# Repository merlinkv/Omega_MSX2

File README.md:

# Omega_MSX2
Update of the Omega Home Computer Project

# Original description

This project is an open source implementation of an MSX2 compatible computer. The project is built using a combination of 1980's era components - Z80 CPU, V9958 VDP, AY-3-8910/YM2149F PSG, 8255 PPI, 7400-series logic, and some newer components, such as 512 KiB SRAM and 512 KiB Flash ROM and a few simple programmable logic devices (ATF16V8B SPLDs).

# Keyboard PCB

* 14-04-2024
   - Version updated to 1.2 MKV
   - Schematics, PCB and Gerbers successfully ported to KiCad 8.0.1
   - The board has been rerouted.
   - Some components are now SMD
   - [Interactive BOM](https://htmlpreview.github.io/?https://github.com/merlinkv/Omega_MSX2/blob/main/Omega%20MSX%20Keyboard%201.2%20MKV.html)

# Mainboard PCB

* 10-05-2024
   - Added positility to select the connection type of Slots pin 44 (by SPDT switch SW3). They can be connected to GND (normal) or to NMI.
   - [Interactive BOM](https://htmlpreview.github.io/?https://github.com/merlinkv/Omega_MSX2/blob/main/Omega%20MSX%20Mainboard%201.2.7%20MKV.html)
* 20-04-2024
   - Version updated to 1.2.7 MKV
   - Power lines design has been changed.
   - Board has been re-routed.
* 14-04-2024
   - Version updated to 1.2.6 MKV
   - Schematics, PCB and Gerbers successfully ported to KiCad 8.0.1
   - The board has been re-routed.

# July 18, 2023

Added new ROMs.

# Mainboard PCB 1.2.5 MKV

* Improved routing parameters resulting on a bit more clear video & audio. In my opinion, before the RGB image was very good, now is really great.
* Power Switch footprint modified to, if desired, allow solder big section wires.
* Added another +5v Extra Power connector. The idea is to use it with horizontal pins and connect one small 4x4cm fan on top of the V9958.
* Board is tested working 100% with F4-FMPAC & o4Mega (4MB RAM) modules, internal Gotek with LCD 16x2 screen, cartridges Carnivore 2 & TDC-600 (floppy controller) at the same time with one **5.2v/3A** PSU

# Mainboard PCB 1.2 MKV

* Added possibility to use up to four different ROMs (two PLCC32 IC's).
* Added extra footprints for ROM selection switches.
* Changed internal FDD power connector to a better position.
* Changed all routing parameters and a couple of silk errors corrected.

# Mainboard PCB 1.1 MKV

Omega Mainboard PCB 1.1 MKV is a variant of the Mainboards 1.4US & 1.4EU by Sergey Kiselev & Jordi Solis

All "standard" capacitors, resistors & inductors are now in SMD 1206 format and placed at the bottom of the PCB.

New footprints for internal/external connections:

* 5-pins connector for DC-DC converter (+5v IN - +12v/-12v OUT)
* 2-pins connector for Power ON-OFF switch
* Two Extra Power connectors +5v (2-pins)
* One Extra Power connector +12v/-12v (3-pins)
* Connector for FM-PAC Module (AMP-GND, 2-pins)
* Connector for FM-PAC Power (+12v/-12v, 3-pins)
* Connector for RGB & Composite video (5-pins)
* Connector for S-Video (3-pins)
* Connector for Audio (Mono, 2-pins)
* Separate connectors for NMI & RESET (2-pins each)
* NMI signal connected to pin 44 of each slots (MSX3 Update?)
* FDD Power Connector (+5v/+12v, 4-pins)

# Notes

* Electrolytic capacitors: I recommend to use High Frequency and Low ESR ones.
* SMD resistors: Best is to use ones with 1% tolerance. All must be 1/4w.
* SMD capacitors: I recommend to use X7R type (10%) or less tolerance.
* ROM: AM29F040, SST39SF040 or compatible IC's can be used.
* SPLD's: ATF16V8B or GAL16V8B can be used without needed to use new jed's.
* For power cable and power switch best is to use wires with big section.
* At the moment I recommend to use one **5.2v/3A PSU**.
* It's possible to use one **5.5v/3A** PSU (near the limits but it's inside the power range).

# Links

* https://www.winuaespanol.com/phpbb3/viewtopic.php?p=13291#p13291
* https://github.com/skiselev/omega
* https://www.va-de-retro.com/foros/viewtopic.php?f=17&t=9304&start=40#p168183
* http://retrowiki.es/viewtopic.php?f=49&t=200037057&start=32#p200145495

# Images

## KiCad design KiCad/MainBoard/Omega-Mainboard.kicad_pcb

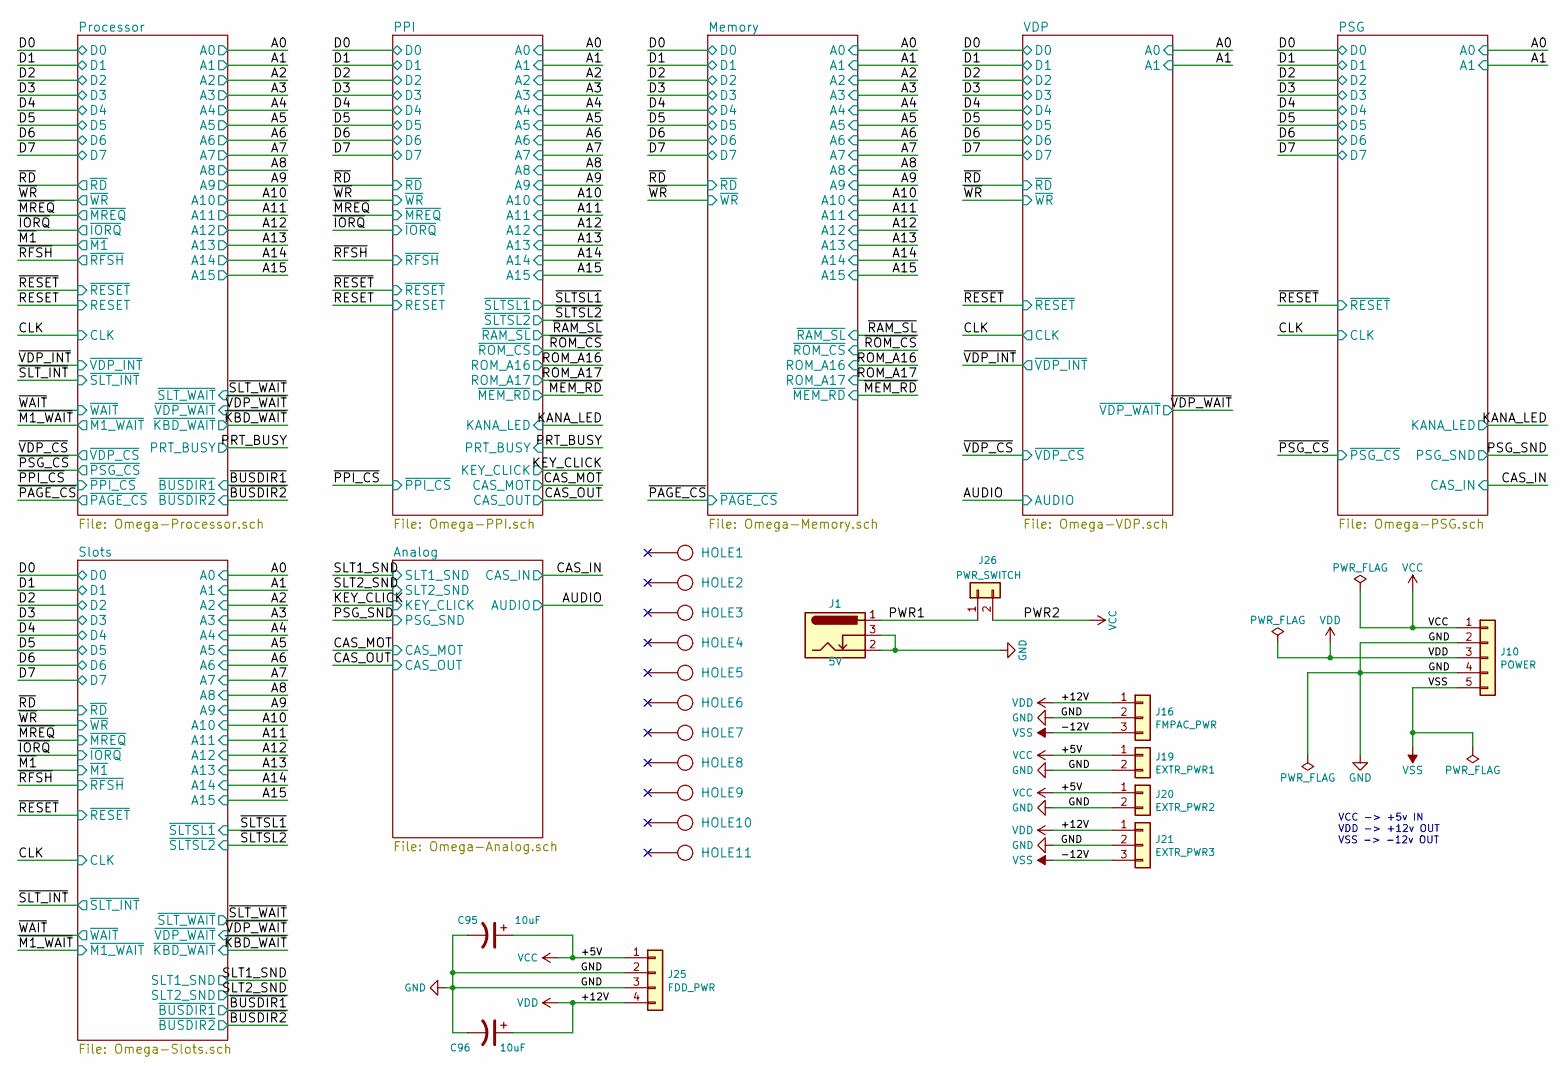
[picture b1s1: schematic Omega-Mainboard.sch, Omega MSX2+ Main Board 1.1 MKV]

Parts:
C95, C96: 10uF; CP_Radial_D5.0mm_P2.50mm
HOLE1, HOLE2, HOLE3, HOLE4, HOLE5, HOLE6, HOLE7, HOLE8, HOLE9, HOLE10, HOLE11: HOLE; MountingHole_3mm_Pad
J1: 5V; BarrelJack_Horizontal
J10: POWER; Molex_KK-254_AE-6410-05A_1x05_P2.54mm_Vertical
J16: FMPAC_PWR; Molex_KK-254_AE-6410-03A_1x03_P2.54mm_Vertical
J19: EXTR_PWR1; Molex_KK-254_AE-6410-02A_1x02_P2.54mm_Vertical
J20: EXTR_PWR2; Molex_KK-254_AE-6410-02A_1x02_P2.54mm_Vertical
J21: EXTR_PWR3; Molex_KK-254_AE-6410-03A_1x03_P2.54mm_Vertical
J25: FDD_PWR; PinHeader_1x04_P2.54mm_Horizontal
J26: PWR_SWITCH; Molex_KK-254_AE-6410-02A_1x02_P2.54mm_Vertical

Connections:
/PWR1: J1.1, J26.1
GND: C95.2, C96.2, J1.2, J1.3, J10.2, J10.4, J16.2, J19.2, J20.2, J21.2, J25.2, J25.3; also elsewhere on the board
VCC: C95.1, J10.1, J19.1, J20.1, J25.1, J26.2; also elsewhere on the board
VDD: C96.1, J10.3, J16.1, J21.1, J25.4; also elsewhere on the board
VSS: J10.5, J16.3, J21.3; also elsewhere on the board

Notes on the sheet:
VCC -> +5v IN VDD -> +12v OUT VSS -> -12v OUT

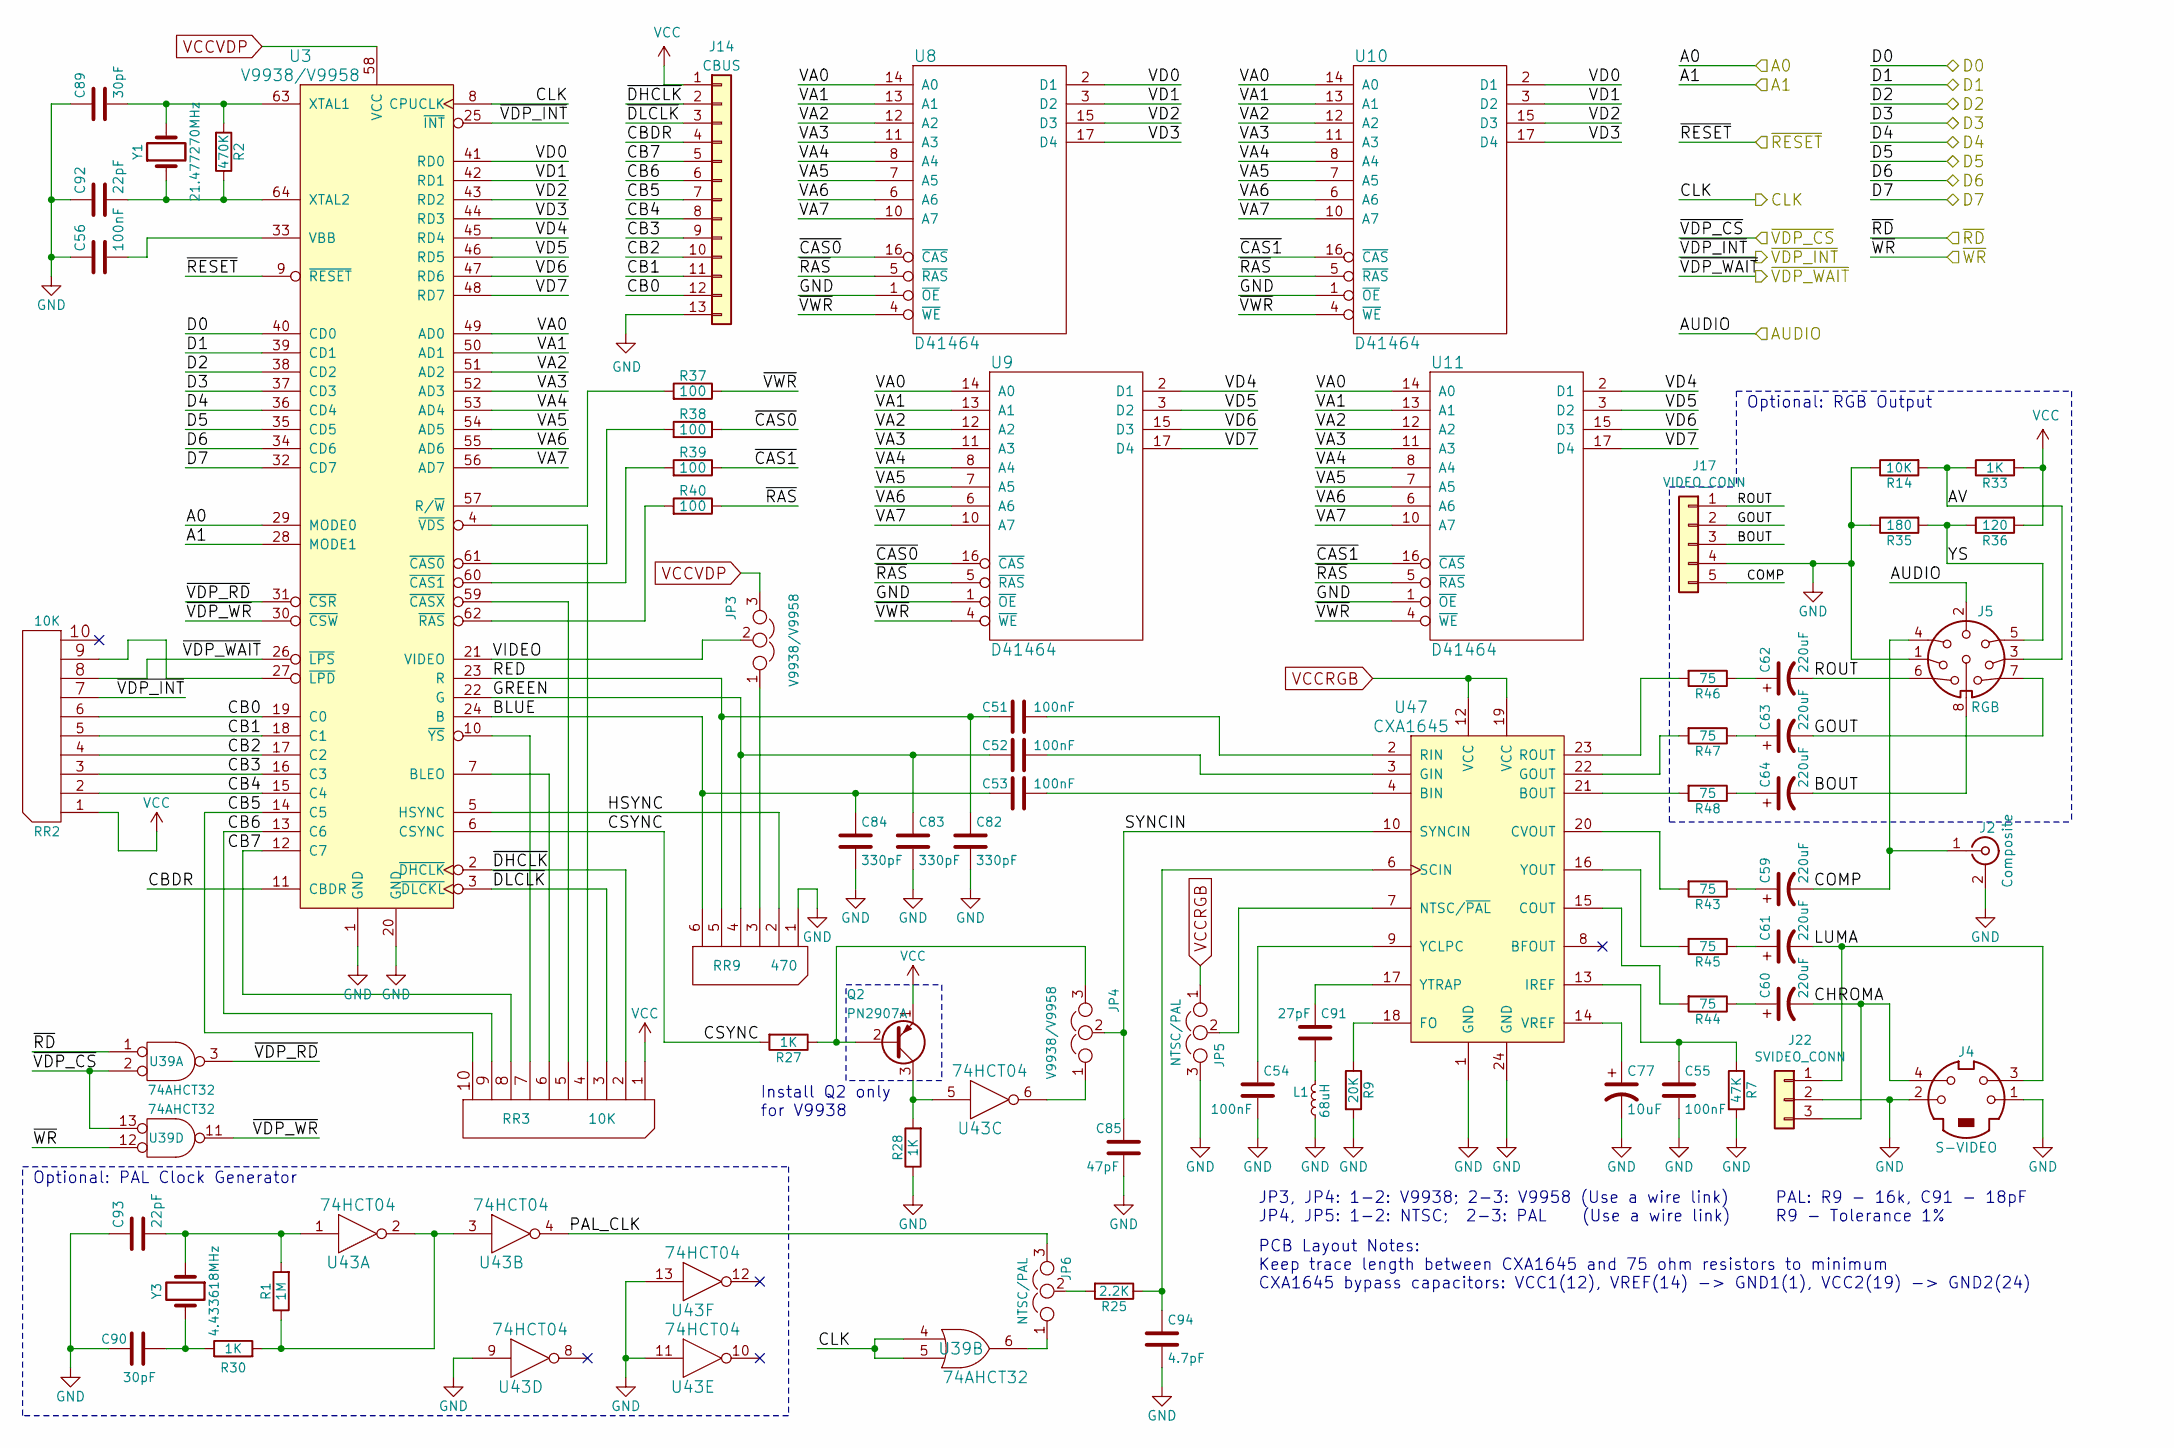
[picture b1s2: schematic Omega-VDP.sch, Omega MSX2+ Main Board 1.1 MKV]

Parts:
C51, C52, C53, C54, C55, C56: 100nF; C_1206_3216Metric_Pad1.42x1.75mm_HandSolder
C59, C60, C61, C62, C63, C64: 220uF; CP_Radial_D10.0mm_P5.00mm
C77: 10uF; CP_Radial_D5.0mm_P2.50mm
C82, C83, C84: 330pF; C_1206_3216Metric_Pad1.42x1.75mm_HandSolder
C85: 47pF; C_1206_3216Metric_Pad1.42x1.75mm_HandSolder
C89, C90: 30pF; C_1206_3216Metric_Pad1.42x1.75mm_HandSolder
C91: 27pF; C_1206_3216Metric_Pad1.42x1.75mm_HandSolder
C92, C93: 22pF; C_1206_3216Metric_Pad1.42x1.75mm_HandSolder
C94: 4.7pF; C_1206_3216Metric_Pad1.42x1.75mm_HandSolder
J2: Composite; Conn_RCA_Right
J4: S-VIDEO; Conn_Mini_DIN_4pin
J5: RGB; DIN8
J14: CBUS; PinHeader_1x13_P2.54mm_Vertical
J17: VIDEO_CONN; Molex_KK-254_AE-6410-05A_1x05_P2.54mm_Vertical
J22: SVIDEO_CONN; Molex_KK-254_AE-6410-03A_1x03_P2.54mm_Vertical
JP3, JP4: V9938/V9958; PinHeader_1x03_P2.54mm_Vertical
JP5, JP6: NTSC/PAL; PinHeader_1x03_P2.54mm_Vertical
L1: 68uH; L_1206_3216Metric_Pad1.42x1.75mm_HandSolder
Q2: PN2907A; TO-92L_Inline_Wide
R1: 1M; R_1206_3216Metric_Pad1.42x1.75mm_HandSolder
R2: 470K; R_1206_3216Metric_Pad1.42x1.75mm_HandSolder
R7: 47K; R_1206_3216Metric_Pad1.42x1.75mm_HandSolder
R9: 20K; R_1206_3216Metric_Pad1.42x1.75mm_HandSolder
R14: 10K; R_1206_3216Metric_Pad1.42x1.75mm_HandSolder
R25: 2.2K; R_1206_3216Metric_Pad1.42x1.75mm_HandSolder
R27, R28, R30, R33: 1K; R_1206_3216Metric_Pad1.42x1.75mm_HandSolder
R35: 180; R_1206_3216Metric_Pad1.42x1.75mm_HandSolder
R36: 120; R_1206_3216Metric_Pad1.42x1.75mm_HandSolder
R37, R38, R39, R40: 100; R_1206_3216Metric_Pad1.42x1.75mm_HandSolder
R43, R44, R45, R46, R47, R48: 75; R_1206_3216Metric_Pad1.42x1.75mm_HandSolder
RR2, RR3: 10K; R_Array_SIP10
RR9: 470; R_Array_SIP6
U3: V9938/V9958; IC_SDIP64_600
U8, U9, U10, U11: D41464; DIP-18_W7.62mm_Socket
U39: 74AHCT32; DIP-14_W7.62mm_Socket
U43: 74HCT04; DIP-14_W7.62mm_Socket
U47: CXA1645; IC_DIP24_400
Y1: 21.477270MHz; Crystal_HC49-U_Vertical
Y3: 4.433618MHz; Crystal_HC49-U_Vertical

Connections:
/A0: U3.29 (MODE0); also elsewhere on the board
/A1: U3.28 (MODE1); also elsewhere on the board
/AUDIO: J5.2; also elsewhere on the board
/CLK: U3.8 (CPUCLK), U39.4, U39.5; also elsewhere on the board
/D0: U3.40 (CD0); also elsewhere on the board
/D1: U3.39 (CD1); also elsewhere on the board
/D2: U3.38 (CD2); also elsewhere on the board
/D3: U3.37 (CD3); also elsewhere on the board
/D4: U3.36 (CD4); also elsewhere on the board
/D5: U3.35 (CD5); also elsewhere on the board
/D6: U3.34 (CD6); also elsewhere on the board
/D7: U3.32 (CD7); also elsewhere on the board
/VDP/AV: J5.3, R14.2, R33.1
/VDP/BLUE: C53.1, C84.1, RR9.6, U3.24 (B)
/VDP/BOUT: C64.2, J5.8, J17.3
/VDP/CB0: J14.12, RR2.6, U3.19 (C0)
/VDP/CB1: J14.11, RR2.5, U3.18 (C1)
/VDP/CB2: J14.10, RR2.4, U3.17 (C2)
/VDP/CB3: J14.9, RR2.3, U3.16 (C3)
/VDP/CB4: J14.8, RR2.2, U3.15 (C4)
/VDP/CB5: J14.7, RR3.10, U3.14 (C5)
/VDP/CB6: J14.6, RR3.9, U3.13 (C6)
/VDP/CB7: J14.5, RR3.8, U3.12 (C7)
/VDP/CBDR: J14.4, U3.11 (CBDR)
/VDP/CHROMA: C60.2, J4.4, J22.3
/VDP/COMP: C59.2, J2.1 (In), J5.4, J17.5
/VDP/CSYNC: R27.2, U3.6 (CSYNC)
/VDP/GOUT: C63.2, J5.7, J17.2
/VDP/GREEN: C52.1, C83.1, RR9.4, U3.22 (G)
/VDP/HSYNC: RR9.2, U3.5 (HSYNC)
/VDP/LUMA: C61.2, J4.3, J22.1
/VDP/PAL_CLK: JP6.3, U43.4
/VDP/RED: C51.1, C82.1, RR9.5, U3.23 (R)
/VDP/ROUT: C62.2, J5.6, J17.1
/VDP/SYNCIN: C85.1, JP4.2, U47.10 (SYNCIN)
/VDP/VA0: U3.49 (AD0), U8.14 (A0), U9.14 (A0), U10.14 (A0), U11.14 (A0)
/VDP/VA1: U3.50 (AD1), U8.13 (A1), U9.13 (A1), U10.13 (A1), U11.13 (A1)
/VDP/VA2: U3.51 (AD2), U8.12 (A2), U9.12 (A2), U10.12 (A2), U11.12 (A2)
/VDP/VA3: U3.52 (AD3), U8.11 (A3), U9.11 (A3), U10.11 (A3), U11.11 (A3)
/VDP/VA4: U3.53 (AD4), U8.8 (A4), U9.8 (A4), U10.8 (A4), U11.8 (A4)
/VDP/VA5: U3.54 (AD5), U8.7 (A5), U9.7 (A5), U10.7 (A5), U11.7 (A5)
/VDP/VA6: U3.55 (AD6), U8.6 (A6), U9.6 (A6), U10.6 (A6), U11.6 (A6)
/VDP/VA7: U3.56 (AD7), U8.10 (A7), U9.10 (A7), U10.10 (A7), U11.10 (A7)
/VDP/VD0: U3.41 (RD0), U8.2 (D1), U10.2 (D1)
/VDP/VD1: U3.42 (RD1), U8.3 (D2), U10.3 (D2)
/VDP/VD2: U3.43 (RD2), U8.15 (D3), U10.15 (D3)
/VDP/VD3: U3.44 (RD3), U8.17 (D4), U10.17 (D4)
/VDP/VD4: U3.45 (RD4), U9.2 (D1), U11.2 (D1)
/VDP/VD5: U3.46 (RD5), U9.3 (D2), U11.3 (D2)
/VDP/VD6: U3.47 (RD6), U9.15 (D3), U11.15 (D3)
/VDP/VD7: U3.48 (RD7), U9.17 (D4), U11.17 (D4)
/VDP/VIDEO: JP3.2, U3.21 (VIDEO)
/VDP/YS: J5.5, R35.2, R36.1
/VDP/~CAS0: R38.1, U8.16 (~CAS), U9.16 (~CAS)
/VDP/~CAS1: R39.1, U10.16 (~CAS), U11.16 (~CAS)
/VDP/~DHCLK: J14.2, RR3.2, U3.2 (~DHCLK)
/VDP/~DLCLK: J14.3, RR3.3, U3.3 (~DLCKL)
/VDP/~RAS: R40.1, U8.5 (~RAS), U9.5 (~RAS), U10.5 (~RAS), U11.5 (~RAS)
/VDP/~VDP_RD: U3.31 (~CSR), U39.3
/VDP/~VDP_WR: U3.30 (~CSW), U39.11
/VDP/~VWR: R37.1, U8.4 (~WE), U9.4 (~WE), U10.4 (~WE), U11.4 (~WE)
/~RD: U39.1; also elsewhere on the board
/~RESET: U3.9 (~RESET); also elsewhere on the board
/~VDP_CS: U39.2, U39.13; also elsewhere on the board
/~VDP_INT: RR2.7, U3.25 (~INT); also elsewhere on the board
/~VDP_WAIT: RR2.8, U3.26 (~LPS); also elsewhere on the board
/~WR: U39.12; also elsewhere on the board
GND: C54.2, C55.2, C56.1, C77.2, C82.2, C83.2, C84.2, C85.2, C89.1, C90.1, C92.1, C93.1, C94.2, J2.2 (Ext), J4.1, J4.2, J5.1, J14.13, J17.4, J22.2, JP5.3, L1.2, R7.2, R9.2, R14.1, R28.1, R35.1, RR9.1 (COM), U3.1 (GND), U3.20 (GND), U8.1 (~OE), U8.18 (GND), U9.1 (~OE), U9.18 (GND), U10.1 (~OE), U10.18 (GND), U11.1 (~OE), U11.18 (GND), U39.7 (GND), U43.7 (GND), U43.9, U43.11, U43.13, U47.1 (GND), U47.24 (GND); also elsewhere on the board
unnamed: C51.2, U47.2 (RIN)
unnamed: C52.2, U47.3 (GIN)
unnamed: C53.2, U47.4 (BIN)
unnamed: C54.1, U47.9 (YCLPC)
unnamed: C55.1, R7.1, U47.13 (IREF)
unnamed: C56.2, U3.33 (VBB)
unnamed: C59.1, R43.1
unnamed: C60.1, R44.1
unnamed: C61.1, R45.1
unnamed: C62.1, R46.1
unnamed: C63.1, R47.1
unnamed: C64.1, R48.1
unnamed: C77.1, U47.14 (VREF)
unnamed: C89.2, R2.2, U3.63 (XTAL1), Y1.2
unnamed: C90.2, R30.1, Y3.2
unnamed: C91.1, U47.17 (YTRAP)
unnamed: C91.2, L1.1
unnamed: C92.2, R2.1, U3.64 (XTAL2), Y1.1
unnamed: C93.2, R1.2, U43.1, Y3.1
unnamed: C94.1, R25.1, U47.6 (SCIN)
unnamed: JP3.1, RR9.3
unnamed: JP4.1, U43.6
unnamed: JP4.3, Q2.2 (B), R27.1
unnamed: JP5.2, U47.7 (NTSC/~PAL)
unnamed: JP6.1, U39.6
unnamed: JP6.2, R25.2
unnamed: Q2.3 (C), R28.2, U43.5
unnamed: R1.1, R30.2, U43.2, U43.3
unnamed: R9.1, U47.18 (FO)
unnamed: R37.2, U3.57 (R/~W)
unnamed: R38.2, U3.61 (~CAS0)
unnamed: R39.2, U3.60 (~CAS1)
unnamed: R40.2, U3.62 (~RAS)
unnamed: R43.2, U47.20 (CVOUT)
unnamed: R44.2, U47.15 (COUT)
unnamed: R45.2, U47.16 (YOUT)
unnamed: R46.2, U47.23 (ROUT)
unnamed: R47.2, U47.22 (GOUT)
unnamed: R48.2, U47.21 (BOUT)
unnamed: RR2.9, U3.27 (~LPD)
unnamed: RR3.4, U3.4 (~VDS)
unnamed: RR3.5, U3.59 (~CASX)
unnamed: RR3.6, U3.7 (BLEO)
unnamed: RR3.7, U3.10 (~YS)
VCC: J14.1, Q2.1 (E), R33.2, R36.2, RR2.1 (COM), RR3.1 (COM), U8.9 (VCC), U9.9 (VCC), U10.9 (VCC), U11.9 (VCC), U39.14 (VCC), U43.14 (VCC); also elsewhere on the board
VCCRGB: JP5.1, U47.12 (VCC), U47.19 (VCC); also elsewhere on the board
VCCVDP: JP3.3, U3.58 (VCC); also elsewhere on the board

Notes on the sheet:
JP3, JP4: 1-2: V9938; 2-3: V9958 (Use a wire link) JP4, JP5: 1-2: NTSC; 2-3: PAL (Use a wire link)
PAL: R9 - 16k, C91 - 18pF R9 - Tolerance 1%
PCB Layout Notes: Keep trace length between CXA1645 and 75 ohm resistors to minimum CXA1645 bypass capacitors: VCC1(12), VREF(14) -> GND1(1), VCC2(19) -> GND2(24)
Optional: PAL Clock Generator
Optional: RGB Output
Install Q2 only for V9938

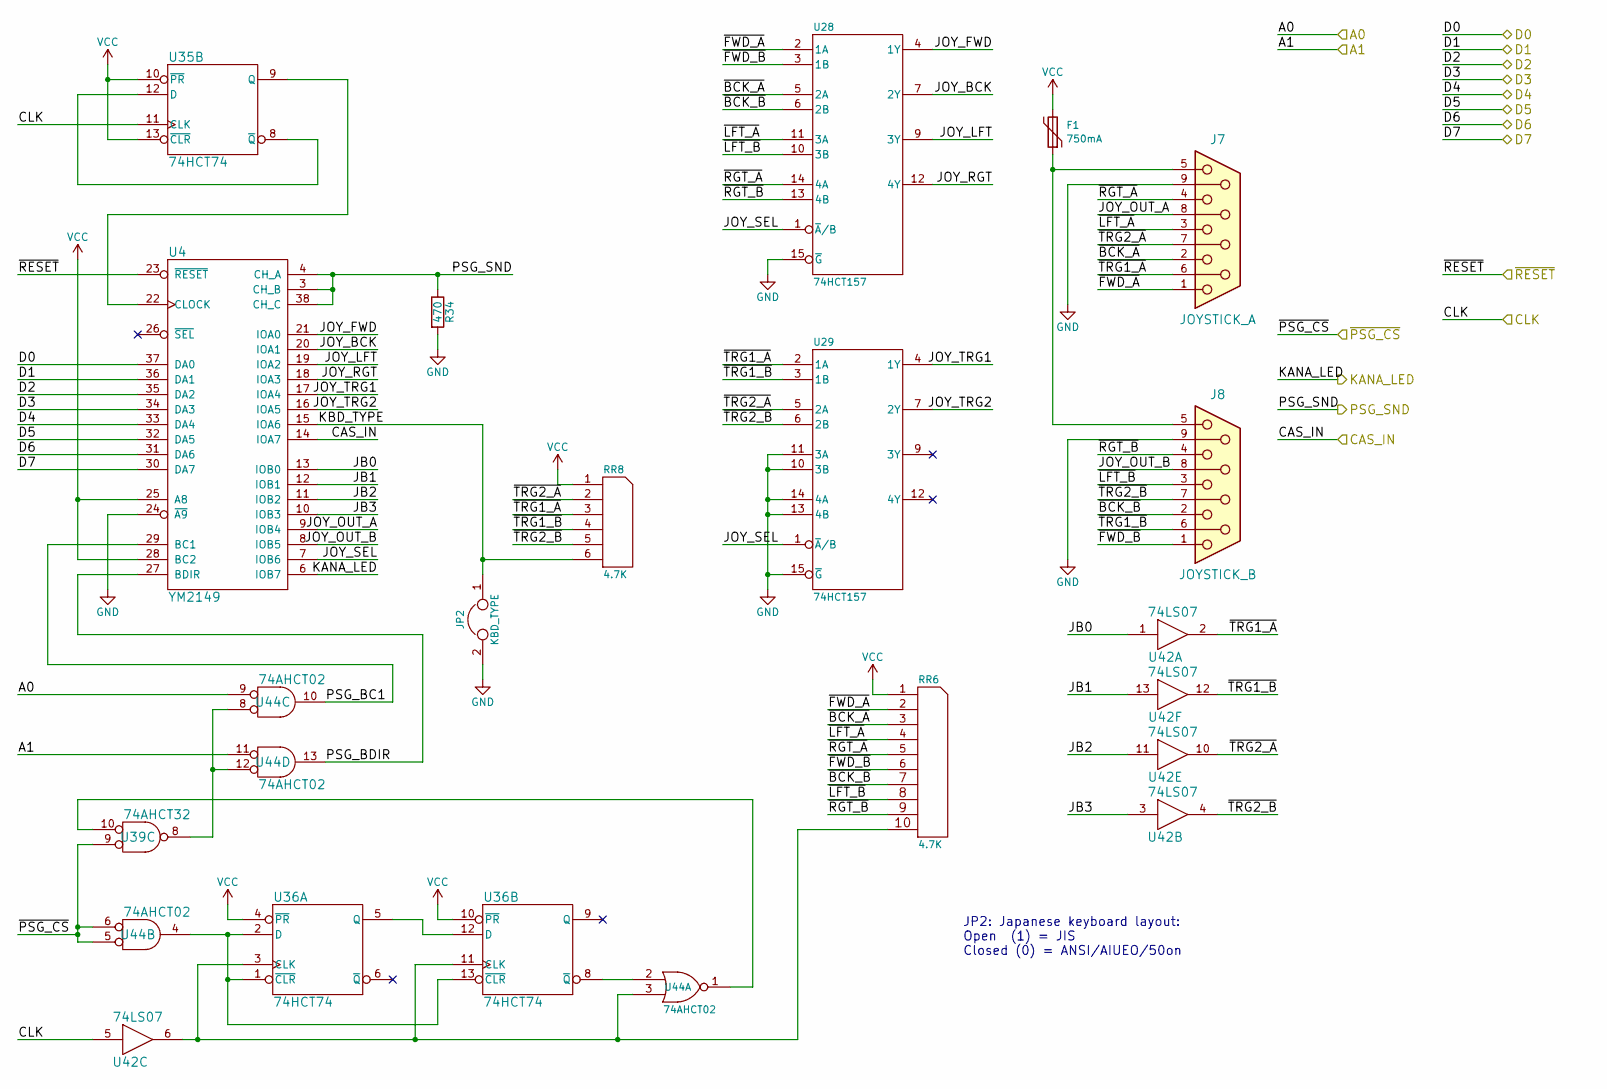
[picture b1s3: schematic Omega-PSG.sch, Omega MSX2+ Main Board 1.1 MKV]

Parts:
F1: 750mA; Fuse_1206_3216Metric_Pad1.42x1.75mm_HandSolder
J7: JOYSTICK_A; DSUB-9_Male_Horizontal_P2.77x2.84mm_EdgePinOffset4.94mm_Hou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
J8: JOYSTICK_B; DSUB-9_Male_Horizontal_P2.77x2.84mm_EdgePinOffset4.94mm_Hou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
JP2: KBD_TYPE; PinHeader_1x02_P2.54mm_Vertical
R34: 470; R_1206_3216Metric_Pad1.42x1.75mm_HandSolder
RR6: 4.7K; R_Array_SIP10
RR8: 4.7K; R_Array_SIP6
U4: YM2149; DIP-40_W15.24mm_Socket
U28, U29: 74HCT157; DIP-16_W7.62mm_Socket
U35, U36: 74HCT74; DIP-14_W7.62mm_Socket
U39: 74AHCT32; IC_DIP14_300
U42: 74LS07; DIP-14_W7.62mm_Socket
U44: 74AHCT02; DIP-14_W7.62mm_Socket

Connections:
/A0: U44.9; also elsewhere on the board
/A1: U44.11; also elsewhere on the board
/CAS_IN: U4.14 (IOA7); also elsewhere on the board
/CLK: U35.11 (CLK), U42.5; also elsewhere on the board
/D0: U4.37 (DA0); also elsewhere on the board
/D1: U4.36 (DA1); also elsewhere on the board
/D2: U4.35 (DA2); also elsewhere on the board
/D3: U4.34 (DA3); also elsewhere on the board
/D4: U4.33 (DA4); also elsewhere on the board
/D5: U4.32 (DA5); also elsewhere on the board
/D6: U4.31 (DA6); also elsewhere on the board
/D7: U4.30 (DA7); also elsewhere on the board
/KANA_LED: U4.6 (IOB7); also elsewhere on the board
/PSG/JB0: U4.13 (IOB0), U42.1
/PSG/JB1: U4.12 (IOB1), U42.13
/PSG/JB2: U4.11 (IOB2), U42.11
/PSG/JB3: U4.10 (IOB3), U42.3
/PSG/JOY_BCK: U4.20 (IOA1), U28.7 (2Y)
/PSG/JOY_FWD: U4.21 (IOA0), U28.4 (1Y)
/PSG/JOY_LFT: U4.19 (IOA2), U28.9 (3Y)
/PSG/JOY_OUT_A: J7.8, U4.9 (IOB4)
/PSG/JOY_OUT_B: J8.8, U4.8 (IOB5)
/PSG/JOY_RGT: U4.18 (IOA3), U28.12 (4Y)
/PSG/JOY_SEL: U4.7 (IOB6), U28.1 (~A~/B), U29.1 (~A~/B)
/PSG/JOY_TRG1: U4.17 (IOA4), U29.4 (1Y)
/PSG/JOY_TRG2: U4.16 (IOA5), U29.7 (2Y)
/PSG/KBD_TYPE: JP2.1, RR8.6, U4.15 (IOA6)
/PSG/PSG_BC1: U4.29 (BC1), U44.10
/PSG/PSG_BDIR: U4.27 (BDIR), U44.13
/PSG/~BCK_A: J7.2, RR6.3, U28.5 (2A)
/PSG/~BCK_B: J8.2, RR6.7, U28.6 (2B)
/PSG/~FWD_A: J7.1, RR6.2, U28.2 (1A)
/PSG/~FWD_B: J8.1, RR6.6, U28.3 (1B)
/PSG/~LFT_A: J7.3, RR6.4, U28.11 (3A)
/PSG/~LFT_B: J8.3, RR6.8, U28.10 (3B)
/PSG/~RGT_A: J7.4, RR6.5, U28.14 (4A)
/PSG/~RGT_B: J8.4, RR6.9, U28.13 (4B)
/PSG/~TRG1_A: J7.6, RR8.3, U29.2 (1A), U42.2
/PSG/~TRG1_B: J8.6, RR8.4, U29.3 (1B), U42.12
/PSG/~TRG2_A: J7.7, RR8.2, U29.5 (2A), U42.10
/PSG/~TRG2_B: J8.7, RR8.5, U29.6 (2B), U42.4
/PSG_SND: R34.1, U4.3 (CH_B), U4.4 (CH_A), U4.38 (CH_C); also elsewhere on the board
/~PSG_CS: U39.9, U44.5, U44.6; also elsewhere on the board
/~RESET: U4.23 (~RESET); also elsewhere on the board
GND: J7.9, J8.9, JP2.2, R34.2, U4.1 (GND), U4.24 (~A9), U28.8 (GND), U28.15 (~G), U29.8 (GND), U29.10 (3B), U29.11 (3A), U29.13 (4B), U29.14 (4A), U29.15 (~G), U35.7 (GND), U36.7 (GND), U39.7 (GND), U42.7 (GND), U44.7 (GND); also elsewhere on the board
unnamed: F1.1, J7.5, J8.5
unnamed: RR6.10, U36.3 (CLK), U36.11 (CLK), U42.6, U44.3
unnamed: U4.22 (CLOCK), U35.9 (Q)
unnamed: U35.8 (~Q), U35.12 (D)
unnamed: U36.1 (~CLR), U36.2 (D), U36.13 (~CLR), U44.4
unnamed: U36.8 (~Q), U44.2
unnamed: U36.5 (Q), U36.12 (D)
unnamed: U39.8, U44.8, U44.12
unnamed: U39.10, U44.1
VCC: F1.2, RR6.1 (COM), RR8.1 (COM), U4.25 (A8), U4.28 (BC2), U4.40 (VCC), U28.16 (VCC), U29.16 (VCC), U35.10 (~PR), U35.13 (~CLR), U35.14 (VCC), U36.4 (~PR), U36.10 (~PR), U36.14 (VCC), U39.14 (VCC), U42.14 (VCC), U44.14 (VCC); also elsewhere on the board

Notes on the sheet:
JP2: Japanese keyboard layout: Open (1) = JIS Closed (0) = ANSI/AIUEO/50on

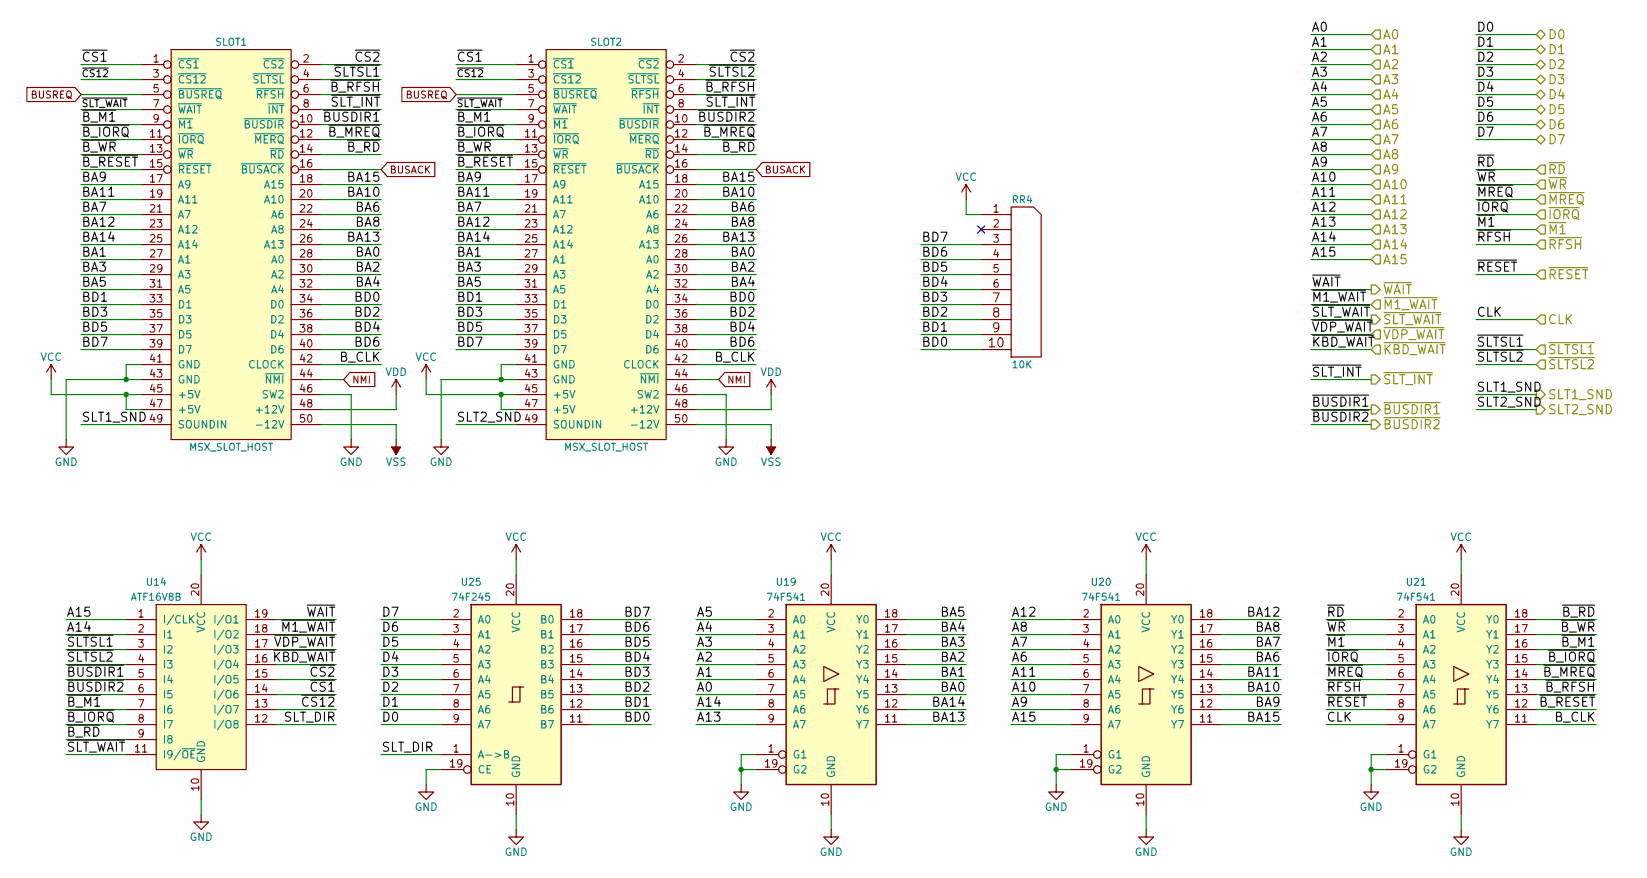
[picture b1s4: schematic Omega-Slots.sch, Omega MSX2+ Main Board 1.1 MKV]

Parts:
RR4: 10K; R_Array_SIP10
SLOT1, SLOT2: MSX_SLOT_HOST; Conn_Edge_50P
U14: ATF16V8B; DIP-20_W7.62mm_Socket
U19, U20, U21: 74F541; DIP-20_W7.62mm_Socket
U25: 74F245; DIP-20_W7.62mm_Socket

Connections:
/A0: U19.7 (A5); also elsewhere on the board
/A1: U19.6 (A4); also elsewhere on the board
/A2: U19.5 (A3); also elsewhere on the board
/A3: U19.4 (A2); also elsewhere on the board
/A4: U19.3 (A1); also elsewhere on the board
/A5: U19.2 (A0); also elsewhere on the board
/A6: U20.5 (A3); also elsewhere on the board
/A7: U20.4 (A2); also elsewhere on the board
/A8: U20.3 (A1); also elsewhere on the board
/A9: U20.8 (A6); also elsewhere on the board
/A10: U20.7 (A5); also elsewhere on the board
/A11: U20.6 (A4); also elsewhere on the board
/A12: U20.2 (A0); also elsewhere on the board
/A13: U19.9 (A7); also elsewhere on the board
/A14: U14.2 (I1), U19.8 (A6); also elsewhere on the board
/A15: U14.1 (I/CLK), U20.9 (A7); also elsewhere on the board
/CLK: U21.9 (A7); also elsewhere on the board
/D0: U25.9 (A7); also elsewhere on the board
/D1: U25.8 (A6); also elsewhere on the board
/D2: U25.7 (A5); also elsewhere on the board
/D3: U25.6 (A4); also elsewhere on the board
/D4: U25.5 (A3); also elsewhere on the board
/D5: U25.4 (A2); also elsewhere on the board
/D6: U25.3 (A1); also elsewhere on the board
/D7: U25.2 (A0); also elsewhere on the board
/SLT1_SND: SLOT1.49 (SOUNDIN); also elsewhere on the board
/SLT2_SND: SLOT2.49 (SOUNDIN); also elsewhere on the board
/Slots/BA0: SLOT1.28 (A0), SLOT2.28 (A0), U19.13 (Y5)
/Slots/BA1: SLOT1.27 (A1), SLOT2.27 (A1), U19.14 (Y4)
/Slots/BA2: SLOT1.30 (A2), SLOT2.30 (A2), U19.15 (Y3)
/Slots/BA3: SLOT1.29 (A3), SLOT2.29 (A3), U19.16 (Y2)
/Slots/BA4: SLOT1.32 (A4), SLOT2.32 (A4), U19.17 (Y1)
/Slots/BA5: SLOT1.31 (A5), SLOT2.31 (A5), U19.18 (Y0)
/Slots/BA6: SLOT1.22 (A6), SLOT2.22 (A6), U20.15 (Y3)
/Slots/BA7: SLOT1.21 (A7), SLOT2.21 (A7), U20.16 (Y2)
/Slots/BA8: SLOT1.24 (A8), SLOT2.24 (A8), U20.17 (Y1)
/Slots/BA9: SLOT1.17 (A9), SLOT2.17 (A9), U20.12 (Y6)
/Slots/BA10: SLOT1.20 (A10), SLOT2.20 (A10), U20.13 (Y5)
/Slots/BA11: SLOT1.19 (A11), SLOT2.19 (A11), U20.14 (Y4)
/Slots/BA12: SLOT1.23 (A12), SLOT2.23 (A12), U20.18 (Y0)
/Slots/BA13: SLOT1.26 (A13), SLOT2.26 (A13), U19.11 (Y7)
/Slots/BA14: SLOT1.25 (A14), SLOT2.25 (A14), U19.12 (Y6)
/Slots/BA15: SLOT1.18 (A15), SLOT2.18 (A15), U20.11 (Y7)
/Slots/BD0: RR4.10, SLOT1.34 (D0), SLOT2.34 (D0), U25.11 (B7)
/Slots/BD1: RR4.9, SLOT1.33 (D1), SLOT2.33 (D1), U25.12 (B6)
/Slots/BD2: RR4.8, SLOT1.36 (D2~), SLOT2.36 (D2~), U25.13 (B5)
/Slots/BD3: RR4.7, SLOT1.35 (D3), SLOT2.35 (D3), U25.14 (B4)
/Slots/BD4: RR4.6, SLOT1.38 (D4), SLOT2.38 (D4), U25.15 (B3)
/Slots/BD5: RR4.5, SLOT1.37 (D5), SLOT2.37 (D5), U25.16 (B2)
/Slots/BD6: RR4.4, SLOT1.40 (D6), SLOT2.40 (D6), U25.17 (B1)
/Slots/BD7: RR4.3, SLOT1.39 (D7), SLOT2.39 (D7), U25.18 (B0)
/Slots/B_CLK: SLOT1.42 (CLOCK), SLOT2.42 (CLOCK), U21.11 (Y7)
/Slots/SLT_DIR: U14.12 (I/O8), U25.1 (A->B)
/Slots/~B_IORQ: SLOT1.11 (~IORQ), SLOT2.11 (~IORQ), U14.8 (I7), U21.15 (Y3)
/Slots/~B_M1: SLOT1.9 (~M1), SLOT2.9 (~M1), U14.7 (I6), U21.16 (Y2)
/Slots/~B_MREQ: SLOT1.12 (~MERQ), SLOT2.12 (~MERQ), U21.14 (Y4)
/Slots/~B_RD: SLOT1.14 (~RD), SLOT2.14 (~RD), U14.9 (I8), U21.18 (Y0)
/Slots/~B_RESET: SLOT1.15 (~RESET), SLOT2.15 (~RESET), U21.12 (Y6)
/Slots/~B_RFSH: SLOT1.6 (~RFSH), SLOT2.6 (~RFSH), U21.13 (Y5)
/Slots/~B_WR: SLOT1.13 (~WR), SLOT2.13 (~WR), U21.17 (Y1)
/Slots/~CS1: SLOT1.1 (~CS1), SLOT2.1 (~CS1), U14.14 (I/O6)
/Slots/~CS2: SLOT1.2 (~CS2), SLOT2.2 (~CS2), U14.15 (I/O5)
/Slots/~CS12: SLOT1.3 (~CS12), SLOT2.3 (~CS12), U14.13 (I/O7)
/~BUSDIR1: SLOT1.10 (~BUSDIR), U14.5 (I4); also elsewhere on the board
/~BUSDIR2: SLOT2.10 (~BUSDIR), U14.6 (I5); also elsewhere on the board
/~IORQ: U21.5 (A3); also elsewhere on the board
/~KBD_WAIT: U14.16 (I/O4); also elsewhere on the board
/~M1: U21.4 (A2); also elsewhere on the board
/~M1_WAIT: U14.18 (I/O2); also elsewhere on the board
/~MREQ: U21.6 (A4); also elsewhere on the board
/~RD: U21.2 (A0); also elsewhere on the board
/~RESET: U21.8 (A6); also elsewhere on the board
/~RFSH: U21.7 (A5); also elsewhere on the board
/~SLTSL1: SLOT1.4 (~SLTSL), U14.3 (I2); also elsewhere on the board
/~SLTSL2: SLOT2.4 (~SLTSL), U14.4 (I3); also elsewhere on the board
/~SLT_INT: SLOT1.8 (~INT), SLOT2.8 (~INT); also elsewhere on the board
/~SLT_WAIT: SLOT1.7 (~WAIT), SLOT2.7 (~WAIT), U14.11 (I9/~OE); also elsewhere on the board
/~VDP_WAIT: U14.17 (I/O3); also elsewhere on the board
/~WAIT: U14.19 (I/O1); also elsewhere on the board
/~WR: U21.3 (A1); also elsewhere on the board
BUSACK: SLOT1.16 (~BUSACK), SLOT2.16 (~BUSACK); also elsewhere on the board
BUSREQ: SLOT1.5 (~BUSREQ), SLOT2.5 (~BUSREQ); also elsewhere on the board
GND: SLOT1.41 (GND), SLOT1.43 (GND), SLOT1.46 (SW2), SLOT2.41 (GND), SLOT2.43 (GND), SLOT2.46 (SW2), U14.10 (GND), U19.1 (G1), U19.10 (GND), U19.19 (G2), U20.1 (G1), U20.10 (GND), U20.19 (G2), U21.1 (G1), U21.10 (GND), U21.19 (G2), U25.10 (GND), U25.19 (CE); also elsewhere on the board
NMI: SLOT1.44 (~NMI), SLOT2.44 (~NMI); also elsewhere on the board
VCC: RR4.1 (COM), SLOT1.45 (+5V), SLOT1.47 (+5V), SLOT2.45 (+5V), SLOT2.47 (+5V), U14.20 (VCC), U19.20 (VCC), U20.20 (VCC), U21.20 (VCC), U25.20 (VCC); also elsewhere on the board
VDD: SLOT1.48 (+12V), SLOT2.48 (+12V); also elsewhere on the board
VSS: SLOT1.50 (-12V), SLOT2.50 (-12V); also elsewhere on the board
